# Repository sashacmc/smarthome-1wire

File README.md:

# smarthome-1wire
Eagle schemes for my first 1-wire boards

See details https://geektimes.ru/post/258212/ (Russian language)

## DS18B20.*
Simple board to provide external power for DS18B20 using 12V line
Fitted to standard phone socket

## DS2408_2PIO_6S_v2.*
My main DS2408 board.
Provide:
* Two 220V outputs.
* Six dry contact (5V) inputs.
* Two ext power (12V).

## DS2408_8S.*
DS2408 only dry contact inputs board.

## warm_floor.*
DS2413 based one channel switch.
Normally controled power 800W (by using passive radiator colling)

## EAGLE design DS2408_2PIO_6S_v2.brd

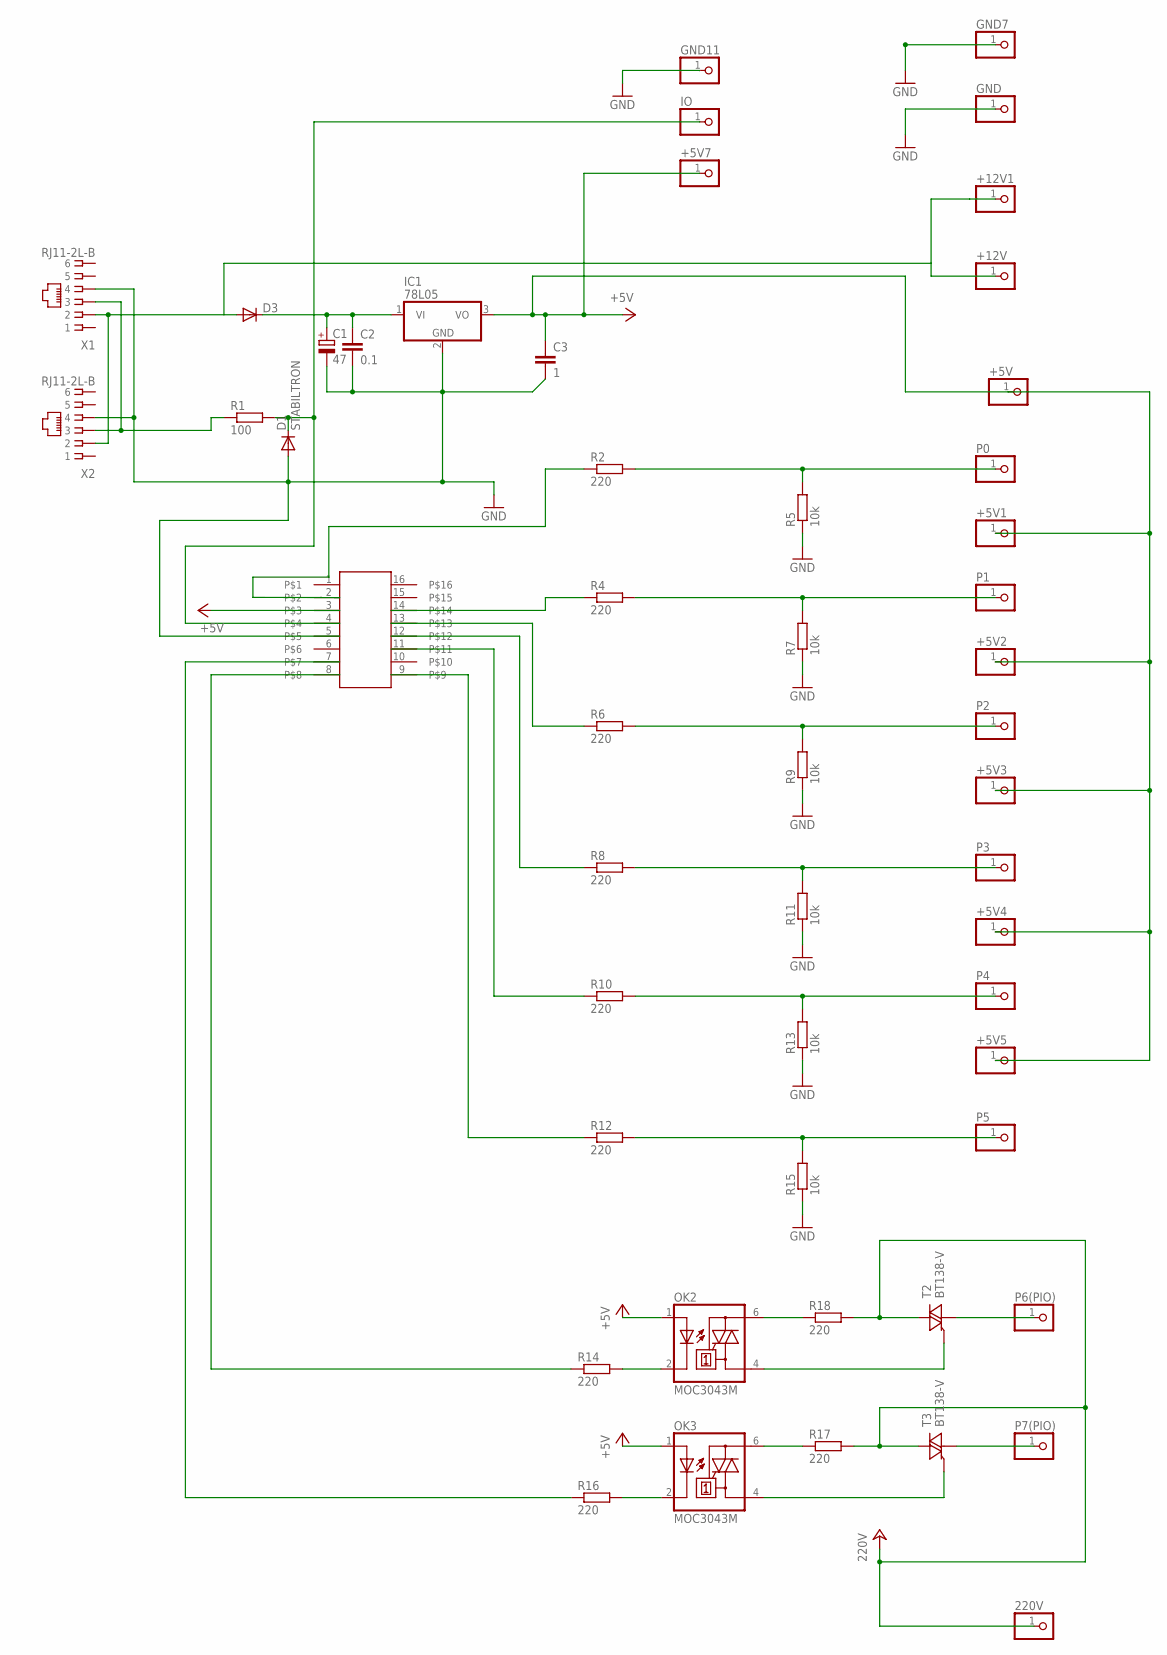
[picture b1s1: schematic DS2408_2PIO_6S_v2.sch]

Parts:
220V: PINHD-1X1; 1X01
+5V, +5V1, +5V2, +5V3, +5V4, +5V5, +5V7, +12V, +12V1: PINHD-1X1; 1X01
C1: 47; E5-10,5
C2: 0.1; C1206
C3: 1; C1206
D1: STABILTRON; DO35-10
D3: DIODE-MINIMELF; MINIMELF
GND, GND7, GND11: PINHD-1X1; 1X01
IC1: 78L05; TO220V
IO: PINHD-1X1; 1X01
OK2, OK3: MOC3043M; DIL06
P0, P1, P2, P3, P4, P5, P6(PIO), P7(PIO): PINHD-1X1; 1X01
R1: 100; M1206
R2, R4, R6, R8, R10, R12, R14, R16, R17, R18: 220; M1206
R5, R7, R9, R11, R13, R15: 10k; M1206
T2, T3: BT138-V; TO220BV
U$1: DS2408S; SO16
X1, X2: RJ11-2L-B; RJ11-NO_SHIELD

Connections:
200V: 220V.1, R17.2, R18.2, T2.T2 (A2), T3.T2 (A2)
+5V: +5V.1, +5V1.1, +5V2.1, +5V3.1, +5V4.1, +5V5.1, +5V7.1, C3.1, IC1.3 (VO), OK2.1 (A), OK3.1 (A), U$1.3
GND: C1.-, C2.2, C3.2, D1.A, GND.1, GND7.1, GND11.1, IC1.2 (GND), R5.1, R7.1, R9.1, R11.1, R13.1, R15.1, U$1.5, X1.4, X2.4
unnamed: +12V.1, +12V1.1, D3.A, X1.2, X2.2
unnamed: R1.1, X1.3, X2.3
unnamed: P1.1, R4.2, R7.2
unnamed: R4.1, U$1.14
unnamed: R14.1, U$1.8
unnamed: OK3.2 (C), R16.2
unnamed: D1.C, IO.1, R1.2, U$1.4
unnamed: P0.1, R2.2, R5.2
unnamed: P2.1, R6.2, R9.2
unnamed: OK2.2 (C), R14.2
unnamed: R12.1, U$1.9
unnamed: P3.1, R8.2, R11.2
unnamed: OK2.6 (A2), R18.1
unnamed: OK3.6 (A2), R17.1
unnamed: P4.1, R10.2, R13.2
unnamed: P5.1, R12.2, R15.2
unnamed: R6.1, U$1.13
unnamed: C1.+, C2.1, D3.C, IC1.1 (VI)
unnamed: OK2.4 (A1), T2.G
unnamed: OK3.4 (A1), T3.G
unnamed: R8.1, U$1.12
unnamed: P6(PIO).1, T2.T1 (A1)
unnamed: P7(PIO).1, T3.T1 (A1)
unnamed: R10.1, U$1.11
unnamed: R16.1, U$1.7
unnamed: R2.1, U$1.2

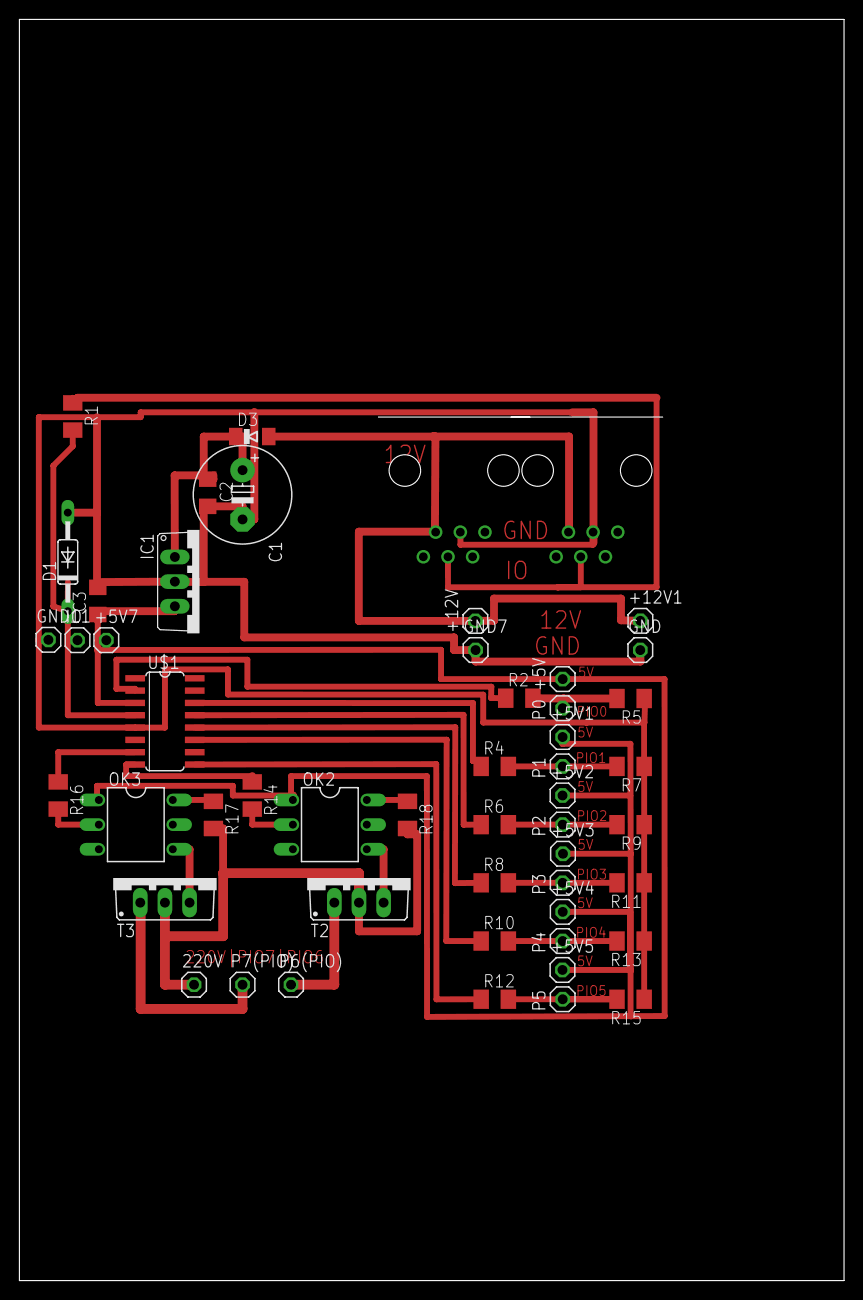
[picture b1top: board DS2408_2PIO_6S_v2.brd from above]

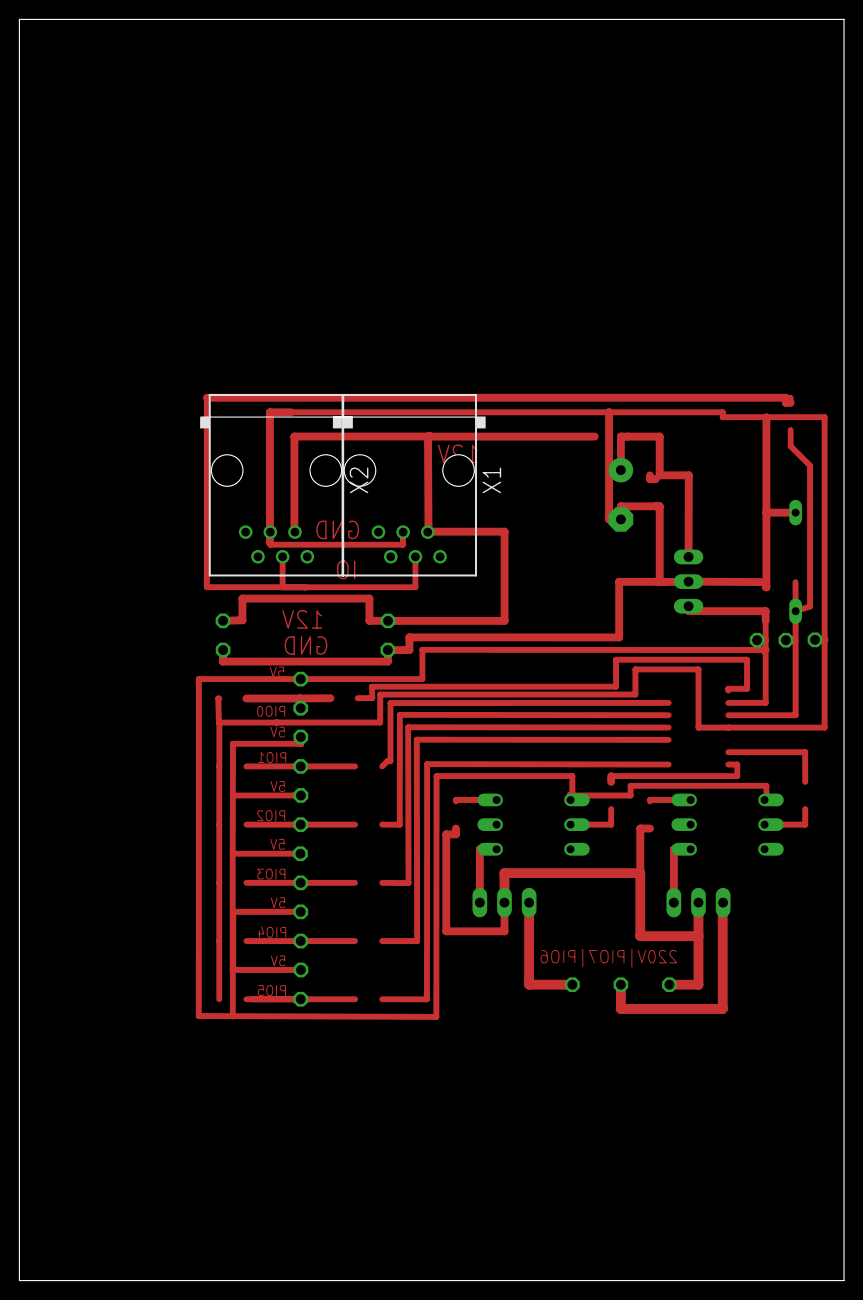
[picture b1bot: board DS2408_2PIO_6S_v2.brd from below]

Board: 2 copper layers, 85.0 x 130.0 mm, 52 parts (2 on the bottom side), 29 nets.

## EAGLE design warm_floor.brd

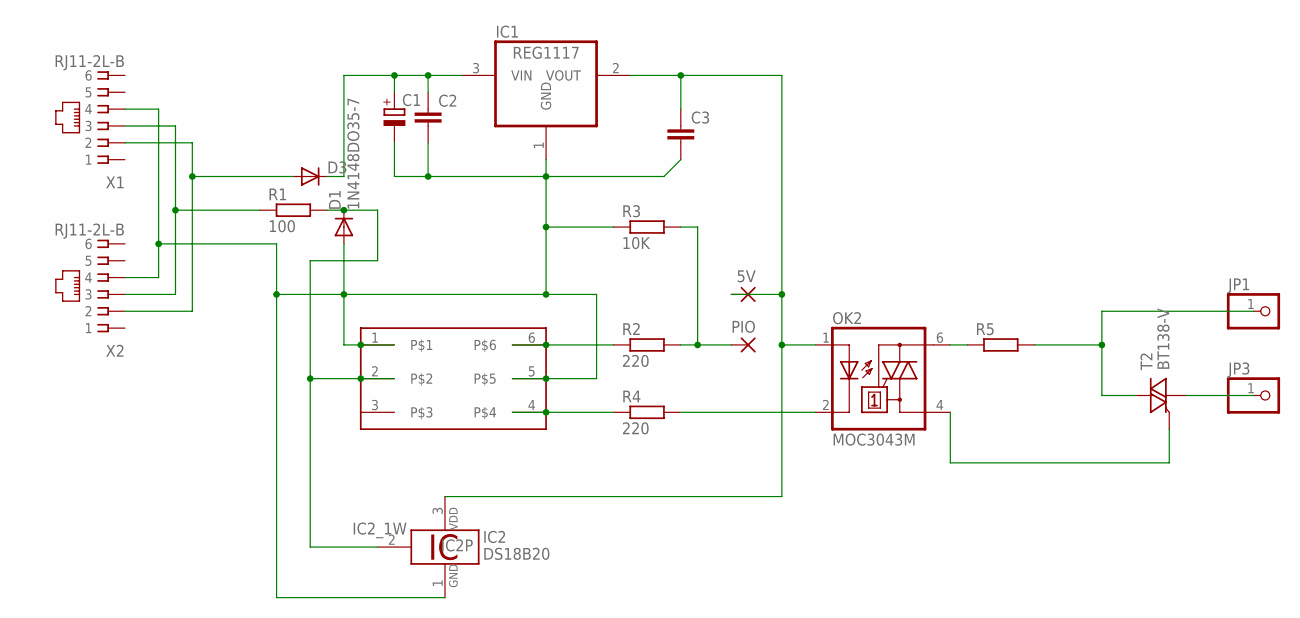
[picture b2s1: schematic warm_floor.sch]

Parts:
5V: 1,6/0,8
C1: CPOL-EUE5-10.5; E5-10,5
C2, C3: C-EUC1206; C1206
D1: 1N4148DO35-7; DO35-7
D3: DIODE-MINIMELF; MINIMELF
DS2413: DS2413P; TSOC6
IC1: REG1117; SOT223
IC2: DS18B20; TO92-
JP1, JP3: PINHD-1X1; 1X01
OK2: MOC3043M; DIL06
PIO: 1,6/0,8
R1: 100; M1206
R2, R4: 220; M1206
R3: 10K; M1206
R5: R-EU_M1206; M1206
T2: BT138-V; TO220BV
X1, X2: RJ11-2L-B; RJ11-NO_SHIELD

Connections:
unnamed: PIO.1, R2.2, R3.2
unnamed: R1.1, X1.3, X2.3
unnamed: D3.A, X1.2, X2.2
unnamed: D1.C, DS2413.2, IC2.2 (1W), R1.2
unnamed: C1.+, C2.1, D3.C, IC1.3 (VIN)
unnamed: 5V.1, C3.1, IC1.2 (VOUT), IC2.3 (VDD), OK2.1 (A)
unnamed: OK2.4 (A1), T2.G
unnamed: DS2413.6, R2.1
unnamed: DS2413.4, R4.1
unnamed: C1.-, C2.2, C3.2, D1.A, DS2413.1, DS2413.5, IC1.1 (GND), IC2.1 (GND), R3.1, X1.4, X2.4
unnamed: OK2.2 (C), R4.2
unnamed: JP1.1, R5.2, T2.T2 (A2)
unnamed: JP3.1, T2.T1 (A1)
unnamed: OK2.6 (A2), R5.1

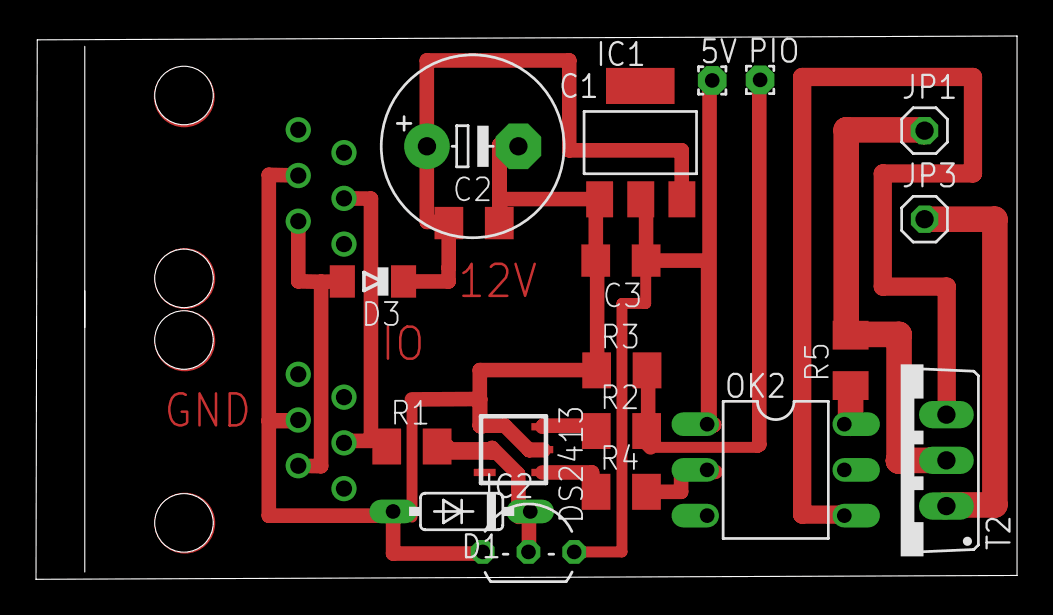
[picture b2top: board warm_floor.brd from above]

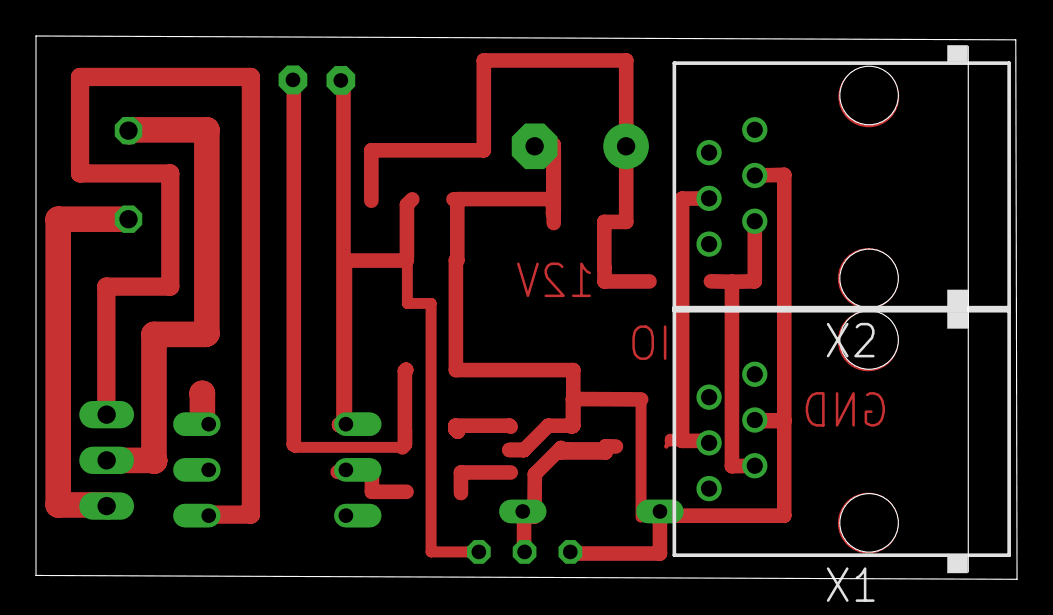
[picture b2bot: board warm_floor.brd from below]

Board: 2 copper layers, 54.5 x 30.2 mm, 21 parts (2 on the bottom side), 14 nets.

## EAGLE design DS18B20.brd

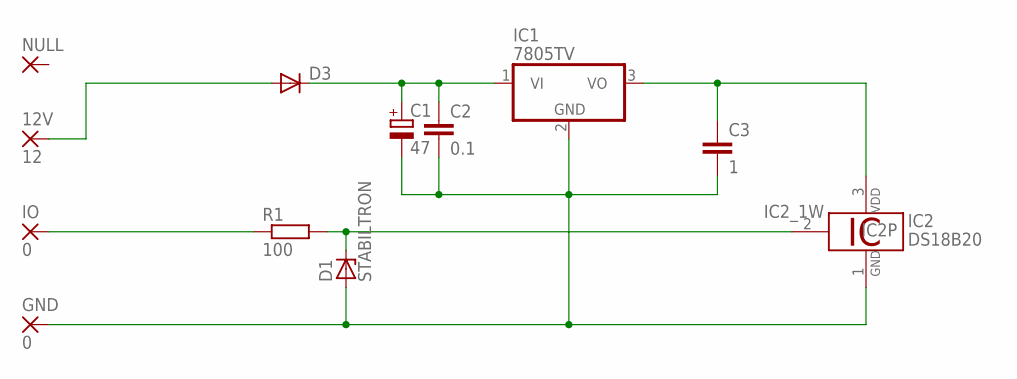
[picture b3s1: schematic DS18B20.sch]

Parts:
12V: 12; 3,81/1,4
C1: 47; E2,5-5
C2: 0.1; C0805
C3: 1; C0805
D1: STABILTRON; SOD80C
D3: DIODE-SOD80C; SOD80C
GND: 0; 3,81/1,4
IC1: 7805TV; TO220V
IC2: DS18B20; TO92-
IO: 0; 3,81/1,4
NULL: 3,81/1,4
R1: 100; R0805

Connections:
unnamed: 12V.1, D3.A
unnamed: IO.1, R1.1
unnamed: C3.1, IC1.3 (VO), IC2.3 (VDD)
unnamed: C1.-, C2.2, C3.2, D1.A, GND.1, IC1.2 (GND), IC2.1 (GND)
unnamed: D1.C, IC2.2 (1W), R1.2
unnamed: C1.+, C2.1, D3.C, IC1.1 (VI)

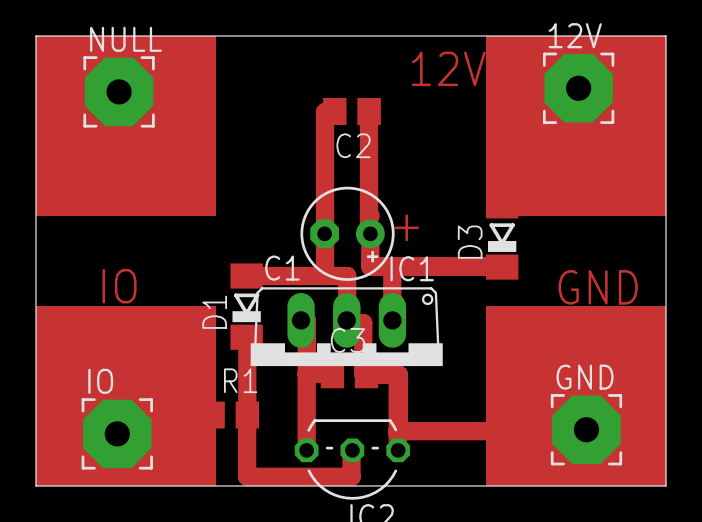
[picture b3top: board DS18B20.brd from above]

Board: 2 copper layers, 35.0 x 25.0 mm, 12 parts (0 on the bottom side), 6 nets.

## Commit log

2017-05-16 Initial release.
